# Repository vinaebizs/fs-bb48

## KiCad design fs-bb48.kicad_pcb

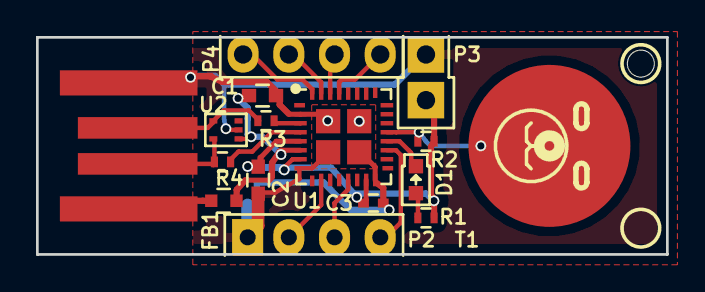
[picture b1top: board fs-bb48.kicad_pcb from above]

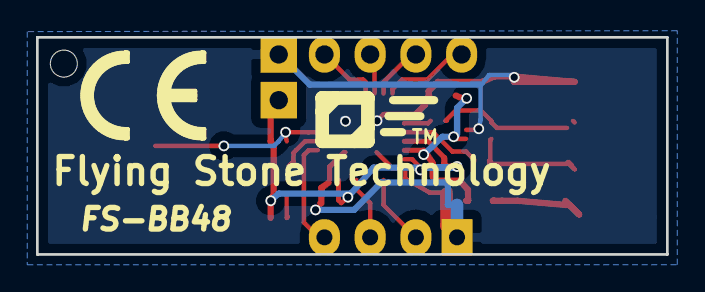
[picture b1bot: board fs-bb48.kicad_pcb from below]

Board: 2 copper layers, 35.0 x 12.1 mm, 19 parts (2 on the bottom side), 18 nets.

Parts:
C1, C2: 2.2uF; C_0603
C3: 0.1uF; C_0402
CE1: CE_5mm; Symbol_CE_SilkScreen_5mm
D1: LED; LED-0603
FB1: 330ohm; FB_SM0603
FST-LOGO: LOGO1; FST-LOGO
H1: Hole
P1: USB; usb-PCB
P2: SWD; Pin_Header_Straight_1x04_A
P3: PWR; Pin_Header_Straight_1x02
P4: EXT; Pin_Header_Straight_1x04
R1: 510R; R_0402
R2: 1M; R_0402
R3, R4: 33R; R_0402
T1: TOUCH_PAD; TOUCH_PAD_9mm
U1: MKL27Z256VFM4; QFN-32-1EP_5x5mm_Pitch0.5mm
U2: NUP2114; SOT-553

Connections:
+3V3: C2.1, C3.1, P3.1, R1.2, R2.1, U1.5, U1.7, U1.15
/D+: R3.1, U1.3
/D+_: P1.3, R3.2, U2.4
/D-: R4.1, U1.4
/D-_: P1.2, R4.2, U2.5
/LED: D1.1, U1.20
/PTD4: P4.1, U1.29
/PTD5: P4.2, U1.30
/PTD6: P4.3, U1.31
/PTD7: P4.4, U1.32
/RESET: P2.1, U1.19
/SWD_CLK: P2.3, U1.10
/SWD_DIO: P2.2, U1.13
/TOUCH: R2.2, T1.1, U1.21
/VBUS: C1.1, FB1.2, U1.6, U2.1
/VBUS_: FB1.1, P1.1
GND: C1.2, C2.2, C3.2, P1.4, P2.4, P3.2, U1.2, U1.8, U1.16, U2.2
unnamed: D1.2, R1.1

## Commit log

2016-01-13 Initial design by ASCII.
2016-01-13 start KiCAD project
2016-01-13 Add component library
2016-01-13 Add .gitignore
2016-01-13 move files
2016-01-13 Add schematic.
2016-01-13 Add datasheets
2016-01-13 Add the .kicad_pcb file
2016-01-14 update schematic
2016-01-14 add footprints
2016-01-15 more update
2016-01-15 fix hole size
2016-01-15 solder mask fingerprints change
2016-01-15 Add a script to order fusion PCB
2016-01-15 update dimensions for pcbnew
2016-01-15 Move silks of U1 and U2
2016-01-16 add bare bone animal
2016-01-16 finish BBB
2016-01-16 Added CE marking
2016-01-18 move silks
2016-01-19 Change U2 and make it optional
2016-01-20 Make optional ESD/EMI explicit
2016-01-20 finish change of ESD chip
2016-01-20 each chip is optional
2016-01-20 prettygerbv from fhttp://projects.qi-hardware.com/index.php/p/eda-tools/source/file/master/fab/prettygerbv
2016-01-20 fix prettygerb
2016-01-20 Remove C3, fix FB1, add hole, fix solder paste of U1
2016-01-20 modify VBUS line
2016-01-20 fix GND line
2016-01-21 Fix U1 pads
2016-01-21 Move R4 reference
2016-02-26 tweak USB-A footprint and bear
2016-03-04 update modules and pcb design
2016-03-04 USB PCB connector footprint modification
2016-07-01 Change USB connector pattern, move CE mark, extend copper backside, tweak a via
2016-07-04 Fix file extentions for newer KiCAD
2016-07-04 Add generated files under output/
2016-07-05 Add schematic PDF and BOM-csv for PCBA.
